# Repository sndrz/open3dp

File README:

A RepStrap open 3d printer project.

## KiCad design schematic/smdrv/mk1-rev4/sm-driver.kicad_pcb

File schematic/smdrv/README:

Stepper motor driver PCB

*** open3dp-mk.1-rev.5-0

Rerouted rev.4 with less wires, larger PCB size and correct holes sizes for components.

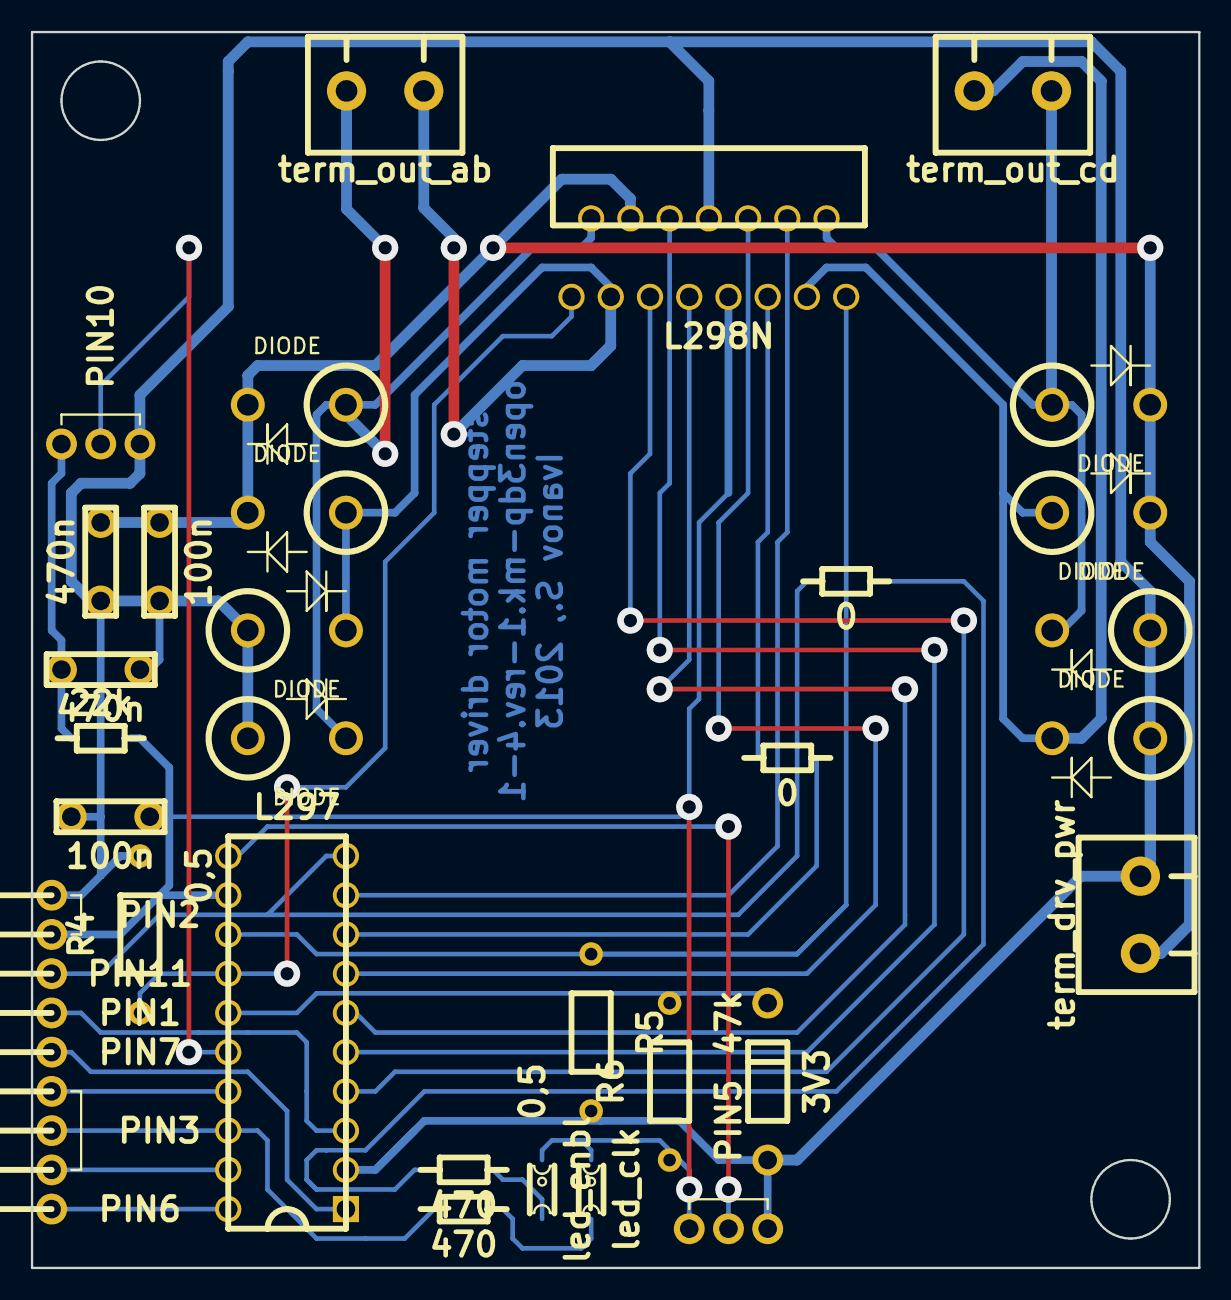
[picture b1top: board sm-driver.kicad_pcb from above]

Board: 2 copper layers, 75.6 x 80.0 mm, 36 parts (0 on the bottom side), 30 nets.

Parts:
C1, C3: 470n; C_CERAM
C2, C4: 100n; C_CERAM
D1, D2, D3, D4, D5, D6, D7, D8: DIODE; DO-201AD_v
D9: 3V3; DO-41_h
LED1: led_enbl; LED_1206
LED2: led_clk; LED_1206
PIN1: pin_home; PIN_1x1-corn
PIN2: pin_ttl_pwr; PIN_2x1-corn
PIN3: pin_drv_ctrl; PIN_3x1-corn
PIN4: term_drv_pwr; DG300-5.0-02P-12
PIN5: pin_switch_ctrl; PIN_3x1
PIN6: pin_rst; PIN_1x1-corn
PIN7: pin_sync; PIN_1x1-corn
PIN8: term_out_ab; DG300-5.0-02P-12
PIN9: term_out_cd; DG300-5.0-02P-12
PIN10: osc_src; PIN_3x1
PIN11: pin_enbl; PIN_1x1-corn
R1, R2: 470; RES_1206
R3: 22k; RES_1206
R4, R5: 0,5; R_5mm_hor
R6: 47k; R_5mm_hor
R7, R8: 0; RES_1206
U1: L297; DIP-20
U2: L298N; multiwatt15v

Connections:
+5V: C2.2, LED1.2, LED2.2, PIN2.2, PIN5.1, R3.1, R6.2, U1.12, U2.9
+36V: C3.1, C4.2, D1.2, D3.2, D5.2, D7.2, PIN4.1, U2.4
GND: C1.2, C2.1, C3.2, C4.1, D2.1, D4.1, D6.1, D8.1, D9.1, PIN2.1, PIN4.2, PIN5.3, PIN10.3, R4.1, R5.1, U1.2, U2.8
unnamed: D7.1, D8.2, PIN9.1, U2.14
unnamed: PIN5.2, U1.11
unnamed: LED1.1, R1.2
unnamed: R1.1, R8.2
unnamed: LED2.1, R2.2
unnamed: C1.1, PIN10.1, R3.2
unnamed: PIN7.1, U1.1
unnamed: PIN6.1, U1.20
unnamed: R7.2, U1.8
unnamed: D9.2, R6.1, U1.15
unnamed: PIN1.1, U1.3
unnamed: R7.1, U2.11
unnamed: PIN3.3, U1.19
unnamed: PIN3.1, U1.17
unnamed: PIN10.2, U1.16
unnamed: U1.9, U2.12
unnamed: U1.7, U2.10
unnamed: U1.6, U2.7
unnamed: U1.5, U2.6
unnamed: U1.4, U2.5
unnamed: D1.1, D2.2, PIN8.2, U2.2
unnamed: D5.1, D6.2, PIN9.2, U2.13
unnamed: R4.2, U1.14, U2.1
unnamed: PIN11.1, R8.1, U1.10
unnamed: PIN3.2, R2.1, U1.18
unnamed: R5.2, U1.13, U2.15
unnamed: D3.1, D4.2, PIN8.1, U2.3

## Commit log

2013-09-18 initial files dump
2013-09-19 Add kicad libraries to repo
2013-09-19 Test
2013-09-19 Add some kicad packages
2013-09-22 Add NEMA motor openscad model
2013-09-22 Submodule test
2013-09-24 Small update
2013-09-24 New develop branch
2013-09-24 Routing in progress
2013-09-25 sm-srv milestone
2013-09-29 Add some MCU code
2013-09-29 Add readme for smdrv
2013-09-30 smdrv-rev.4-1 release
2013-10-02 Update core and power source schematics
2013-10-06 Change pwr src schematic arch
2013-12-20 3dp-mon initial upload
2013-12-20 3dp-mon mwindow files update
2013-12-22 sgit application test
2013-12-23 3dp-mon gui update
2013-12-23 Add 3dp-mon core.* templates
2013-12-23 Add motor.* files
2013-12-26 Cosmetic firmware update
2013-12-27 Add .gitignore
2014-01-12 Add core firmware small code changes.
2014-01-15 Add some code for confuration registers and gcode buffer
2014-01-16 Add some code for g-code buffer
2014-01-17 Add HAL to code
2014-01-17 Add small changes to HAL
2014-01-18 Small changes (submodules init)
2014-01-20 Add Qt project
2014-01-21 Update 3dp-mon code: main window, core classes
2014-01-21 Add comments for core firmware code
2014-01-24 Small changes
2014-02-13 Restructure models directories
2014-02-13 Add chanded smdrv schematic files (looks like dump change)
2014-02-13 Add SW model details
2014-02-20 Update SW model
2014-03-19 Another total constuction
2014-03-19 Rename given by mistake
2014-03-21 Update design
2014-03-27 Update SW design
2014-03-28 Update core schematics
2014-03-31 Delete .gitmodules
    Instead of that -- use modules (examp. kicad-lib and avr-toolbox) laying one
    level with open3d folder (git folder: open3d, kicad-lib, avr-toolbox,
    etc.)
2014-03-31 Add bearings parts to SW design
2014-04-02 smdrv. Add old-style board format
2014-04-02 Update firmware file structure
2014-04-04 Update firmware
2014-04-09 Update co-core firmware
2014-05-20 Start new mk3 design
2014-05-28 Update mk3 design
2014-06-30 smdrv: switch to rev.5 with folder restructure
2014-07-03 smdrv rev.5 pcb routing update
2016-05-26 Switch to autocad
2016-05-27 Update mk.4 design: detaling, layers.
2016-05-31 Update mk.4 design.
2016-06-01 Update mk.4 design drafts.
2016-06-02 Start new mk.4 schematic.
2016-06-02 Detailing nema17
2016-06-07 Update mk.4 core schematics.
2016-06-08 Update mk.4 schematics.
2016-06-09 Update mk.4 core schematic.
2016-10-20 Clear and reorganize whole repo.
2016-10-20 New loop of core schematic.
2017-09-15 Start new design mk1 iteration instead of prototypes.
2017-09-15 Redesign step motor driver mk.1
2017-09-17 Start to redesign motor driver to mk.1
2017-09-18 Finish motor driver mk.1 redesign. Prepare to route PCB.
2017-09-19 Prepare motor driver mk.1 for prototyping.
2017-09-22 Switch to 12V power.
2017-12-29 Update mk1 design
